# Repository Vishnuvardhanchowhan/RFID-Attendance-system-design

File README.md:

# RFID-Attendance-system-design
The project revolves around the development of an RFID-based attendance management system utilizing an MFRC522 chip and TIVA C microcontroller. The system consists of a reader module, tags, and a database, aiming to efficiently mark attendance by reading RFID tags and updating information to a central database.

Key Components and Functionality:
1. Hardware Design: The schematic designs involve integrating the MFRC522 chip onto a PCB with a trace antenna and efficient match filter for noise suppression. A 3D-printed enclosure is used to house the internal circuit.
2. Software Implementation: The TIVA C microcontroller is programmed in embedded C to communicate with the MFRC522 chip via SPI. Libraries for MFRC522 are adapted for use with TIVA C. Various systems like attendance marking, registration, and de-registration are coded into the microcontroller.
3. Test Setup and Results: The system is successfully tested with a setup where RFID cards are scanned, and attendance is marked. Unregistered cards prompt registration, and registered cards mark attendance. Results indicate a 95% accuracy rate in a sample size of 20 cards.
4. Future Work Scope: Future enhancements include improving security through multi-factor authentication, enhancing portability, integrating with access control systems, and expanding functionality to cover areas like inventory management.

Conclusion:
The project achieves its objectives of developing an RFID-based attendance management system. It successfully marks attendance, registers new users, and allows for de-registration. While the system performs well in tests, there's room for improvement in security and functionality, which could be addressed in future iterations. Overall, the system is deemed ready for practical implementation in educational settings.

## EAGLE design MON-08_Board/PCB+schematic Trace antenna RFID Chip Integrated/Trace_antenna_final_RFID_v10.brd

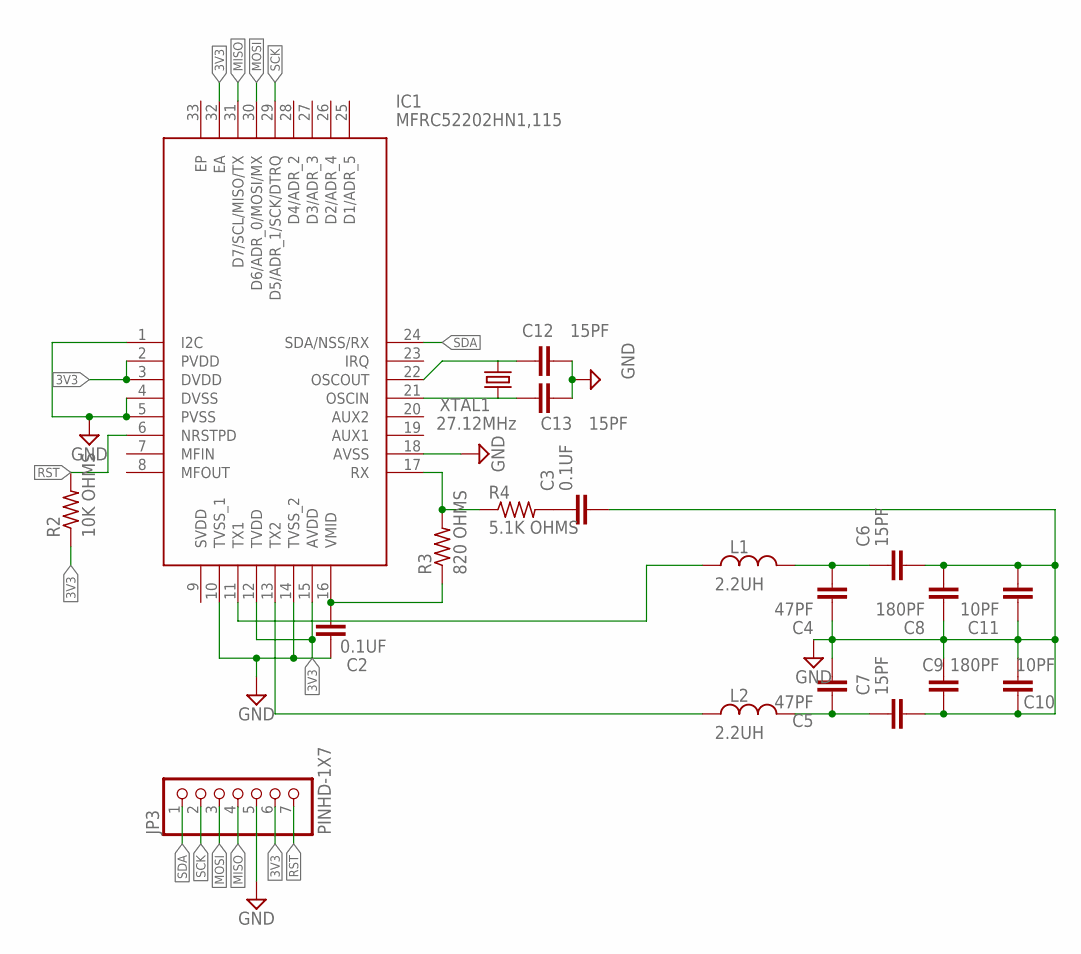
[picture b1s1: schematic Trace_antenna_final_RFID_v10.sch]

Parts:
C2, C3: 0.1UF; CAPC2012X110
C4, C5: 47PF; CAPC2012X110
C6, C7, C12, C13: 15PF; CAPC2012X110
C8, C9: 180PF; CAPC2012X110
C10, C11: 10PF; CAPC2012X110
IC1: MFRC52202HN1,115; QFN50P500X500X100-33N
JP3: PINHD-1X7; 1X07
L1, L2: 2.2UH; INDC2009X120
R2: 10K OHMS; RESC2012X65
R3: 820 OHMS; RESC2012X65
R4: 5.1K OHMS; RESC2012X65
XTAL1: 27.12MHz; XTALRR488W45L1150T500H350B

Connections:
3V3: IC1.2 (PVDD), IC1.3 (DVDD), IC1.12 (TVDD), IC1.15 (AVDD), IC1.32 (EA), JP3.6, R2.1
GND: C2.1, C3.2, C4.1, C5.2, C6.2, C7.2, C8.1, C8.2, C9.1, C9.2, C10.1, C10.2, C11.1, C11.2, C12.2, C13.2, IC1.1 (I2C), IC1.4 (DVSS), IC1.5 (PVSS), IC1.10 (TVSS_1), IC1.14 (TVSS_2), IC1.18 (AVSS), JP3.5
MISO: IC1.31 (D7/SCL/MISO/TX), JP3.4
MOSI: IC1.30 (D6/ADR_0/MOSI/MX), JP3.3
unnamed: C2.2, IC1.16 (VMID), R3.1
unnamed: IC1.11 (TX1), L1.1
unnamed: C12.1, IC1.22 (OSCOUT), XTAL1.2
unnamed: C13.1, IC1.21 (OSCIN), XTAL1.1
unnamed: C4.2, C6.1, L1.2
unnamed: IC1.17 (RX), R3.2, R4.1
unnamed: IC1.13 (TX2), L2.1
unnamed: C5.1, C7.1, L2.2
unnamed: C3.1, R4.2
RST: IC1.6 (NRSTPD), JP3.7, R2.2
SCK: IC1.29 (D5/ADR_1/SCK/DTRQ), JP3.2
SDA: IC1.24 (SDA/NSS/RX), JP3.1

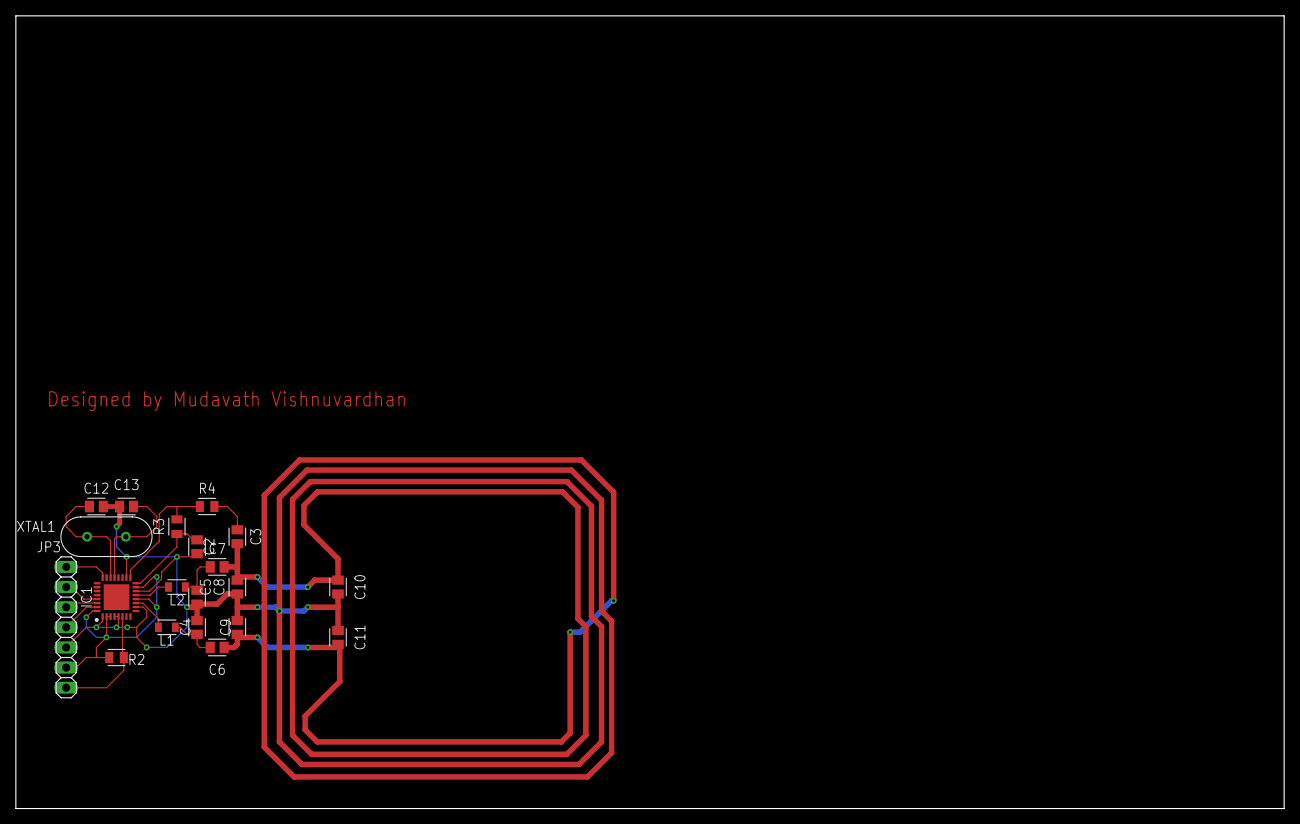
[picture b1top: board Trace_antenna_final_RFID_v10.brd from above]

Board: 2 copper layers, 160.0 x 100.0 mm, 20 parts (0 on the bottom side), 16 nets.

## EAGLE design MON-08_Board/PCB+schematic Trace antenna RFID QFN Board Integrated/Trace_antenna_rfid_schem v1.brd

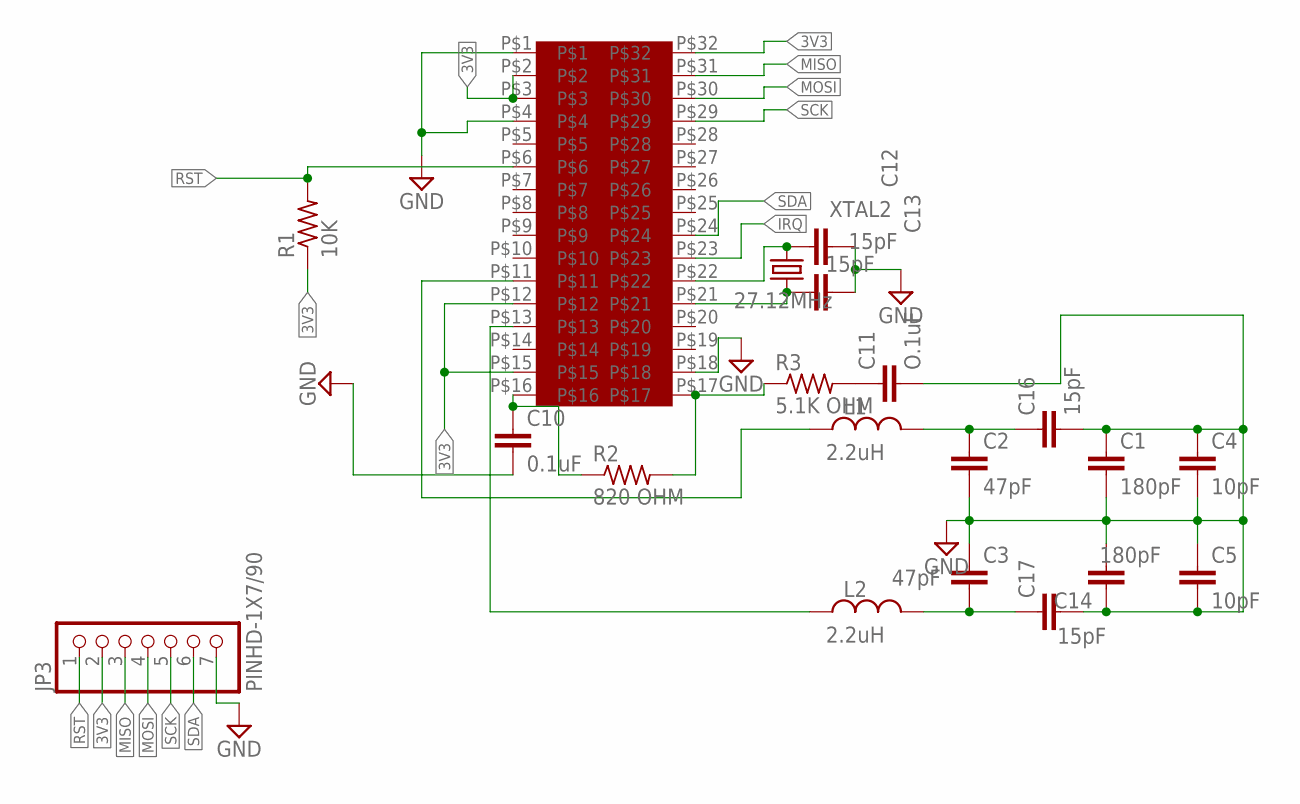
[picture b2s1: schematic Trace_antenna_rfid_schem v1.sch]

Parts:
C1, C14: 180pF; C1206
C2, C3: 47pF; C1206
C4, C5: 10pF; C1206
C10: 0.1uF; C1206
C11: O.1uF; C1206
C12, C13, C16, C17: 15pF; C1206
JP3: PINHD-1X7/90; 1X07/90
L1, L2: 2.2uH; INDC3216X190
R1: 10K; M1206
R2: 820 OHM; M1206
R3: 5.1K OHM; M1206
U$1: MFRC522_BREAKOUTBOARD; BREAKOUT_BOARD_MFRC522
XTAL2: 27.12MHz; XTALRR488W45L1150T500H350B

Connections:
3V3: JP3.2, R1.1, U$1.P$2, U$1.P$3, U$1.P$12, U$1.P$15, U$1.P$32
GND: C1.1, C1.2, C2.2, C3.1, C4.1, C4.2, C5.1, C5.2, C10.2, C11.2, C12.2, C13.2, C14.1, C14.2, C16.2, C17.2, JP3.7, U$1.P$1, U$1.P$4, U$1.P$18
IRQ: U$1.P$23
MISO: JP3.3, U$1.P$31
MOSI: JP3.4, U$1.P$30
unnamed: C2.1, C16.1, L1.2
unnamed: C3.2, C17.1, L2.2
unnamed: C10.1, R2.1, U$1.P$16
unnamed: R2.2, R3.1, U$1.P$17
unnamed: C11.1, R3.2
unnamed: C13.1, U$1.P$21, XTAL2.1
unnamed: C12.1, U$1.P$22, XTAL2.2
unnamed: L2.1, U$1.P$13
unnamed: L1.1, U$1.P$11
RST: JP3.1, R1.2, U$1.P$6
SCK: JP3.5, U$1.P$29
SDA: JP3.6, U$1.P$24

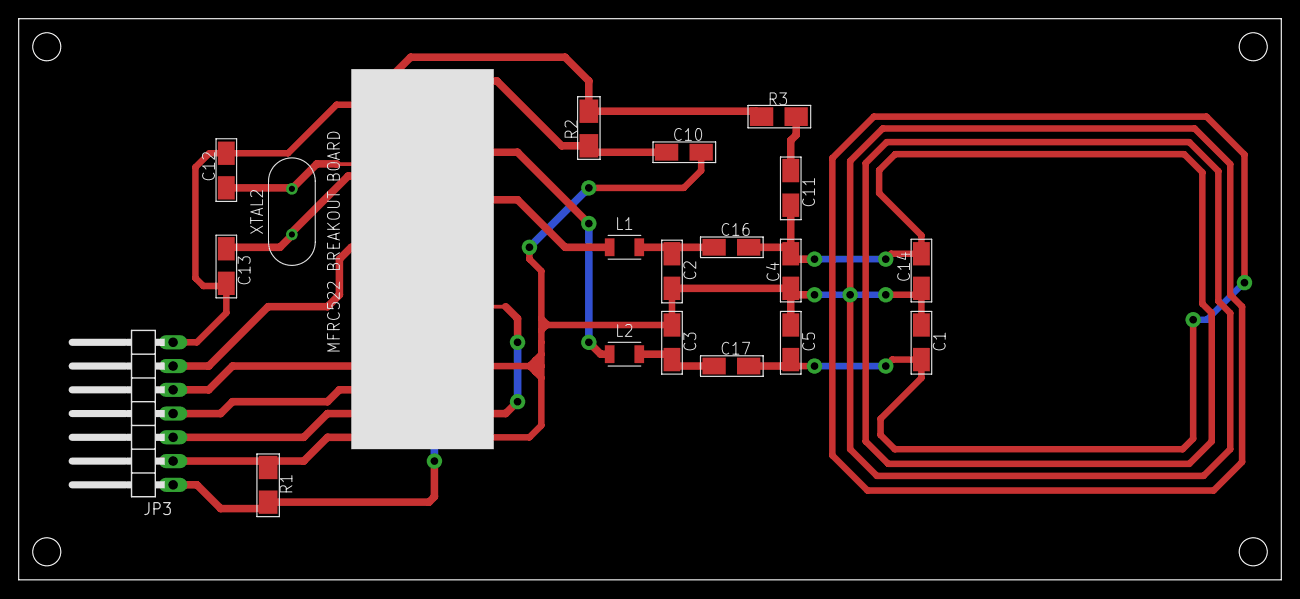
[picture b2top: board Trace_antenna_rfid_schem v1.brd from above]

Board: 2 copper layers, 135.0 x 60.0 mm, 20 parts (0 on the bottom side), 16 nets.
